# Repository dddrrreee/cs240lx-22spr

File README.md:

## CS240lx: advanced operating system lab, accelerated
### Engler + Akshay, Spr 2022.

tl;dr index:

  - [This is a lab class and here are the labs](./labs/README.md).
  - [Course website](https://github.com/dddrrreee/cs240lx-22spr).
  - [Course newsgroup](https://github.com/dddrrreee/cs240lx-22spr).
  - To get the repository: 

        git clone git@github.com:dddrrreee/cs240lx-22spr.git

    Put the path to the repo in your shell startup file:

    E.g. for `tcsh` I put the following in my `.tcshrc` file (and
    did `source ~/.tcshrc` after):
 
        setenv CS240LX_2022_PATH /home/engler/class/cs240lx-22spr/

    If these steps worked, you should be able to type `make` and have
    it work.

This is a implementation-heavy, lab-based class that will cover similar
topics as CS240 --- threads, virtual memory, file systems and distributed
systems --- but by writing code versus discussing papers.  After taking an
initial operating systems course you are often left in the odd situation
of having spent significant time getting the background knowledge needed
to do interesting actions, but not being left with enough time to actually
do them.  This course attacks this problem by assuming basic knowledge and
using it as a springboard to advance quickly through a set of powerful,
useful techniques that even advanced practioners can be ignorant of.

We will write custom code from scratch for the widely-used, ARM-based
raspberry pi; our code will run "bare-metal" without an operating system,
which means we can do interesting things without constantly fighting
with a lumbering OS that cannot get out of its own way.

By combining research insights (many unpublished) and our our lightweight
bare-metal code we will be in the unusual position of having foundational
abilities that most people have assumed are in-practice impossible.
As one example, we will implement fast, flexible exception handling
and then use this ability to build a variety of tools that find race
conditions, check code correctness, and memory  corruption.  By using
exceptions rather than binary rewriting we can build tools that find
similar errors as Purify / Valgrind, but can be implemented in merely
hundreds rather than hundreds of thousands of lines of code; our tools
will also be faster and more extensible.

Our initial plan was to do ten projects, one per week, where each project
covers two labs of (at a minimum) several hours each and a non-trivial
amount of outside work.

The course workload is significant, but I will aim to not waste your time.
CS140E is strongly encouraged as a prerequisite, but a sufficiently
talented and motivated implementor can make up for its lack.

I'm teaching this course because doing CS140E was was so much fun.
Each time I drove into lab, I would get an idea for one or two additional
labs I really wanted to do, and each time I wrote up an lab there would
be a long `NOTES.txt` of additional ideas.  After last year and this, I
have a big document of all the possible ideas.  This class will implement
the ones that seem the most interesting.

Also, we have Akshay for another quarter as a TA so it seems sensible
to exploit that happy fact!

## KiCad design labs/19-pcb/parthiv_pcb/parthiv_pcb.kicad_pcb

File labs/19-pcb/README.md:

# PCB (KiCAD) Lab by Parthiv

This lab is focused on designing printed circuit boards (PCBs), which you may find useful in your final project. This is moreso a quick lesson on how to replace your bundles of wires with a more reliable board, rather than how to actually design electrical circuits on a board which is a much more involved discussion. 

Our goal is to create a board that can plug into the Raspberry Pi GPIO header and connect to the USB/UART converter and 2 NRFs. You can also optionally add other devices to the board of your choosing. My board looks something like this:

You can see the GPIO header on the bottom and various headers on the top to connect other devices.

A sample PCB project that contains the board above can be found in `parthiv_pcb/`. You can refer to this if you ever run into a wall for how to proceed.

## Step 0: Installation

Please follow the instructions at [https://www.kicad.org/download/](https://www.kicad.org/download/) for your OS. It is open source so it should be possible but potentially annoying to build if your OS isn't listed.

### General Keyboard Shortcuts
I assume `Ctrl` becomes `Cmd` on mac.

* `Ctrl+S`: Save (do often!)
* `Ctrl+Z`: Undo
* `Ctrl+Y`: Redo
## Step 1: Creating a Project

1. Open up KiCAD (either type `kicad` in your terminal or search for it in your installed applications).
2. Go to File->New Project. Select a location where you want to create the project (you can do it in this directory) and give it a name. Ensure that the box to "Create a new folder for the project" is selected. Create the project.
3. You should see a window like this:

    On the left side, you can see a file called [project_name].kicad_pcb and another file called [project_name].kicad_sch. Double clicking these will open the PCB and Schematic editors respectively. 

## Step 2: Creating your Schematic

1. In the main KiCAD window, double click the .kicad_sch file to open the Schematic editor. You will see a blank schematic:

The schematic is where we will describe what pins of what components connect to what other pins of other components. You should try to keep it relatively organized if you can!

You can middle click and drag to move, or scroll up/down to zoom.

2. Go to Place->Add Symbol (or type the keyboard shortcut `A`). In the search bar, search for the symbol `Raspberry_Pi_2_3`. Select it, then click OK to start placing the component. Place it somewhere in the middle of the schematic by clicking. If you want to move it, you can click on it, hit `M`, and then move it around, then click again to place it. 

3. Now, we will connect the power rails of the Raspberry Pi. Hit `P` to open up the power symbol menu. Look for `GND` and hit OK to start placing the ground symbol. Put it near the bottom of the Raspberry Pi symbol. Hover over the end of one of the GND pins on the Pi, then hit `W` to start drawing a wire. Connect it to the GND symbol you just placed. Repeat this process for all the GND pins (see below).

Next, add power symbols for `+5V` and `+3V3` to the schematic, and connect those to the 5V and 3V3 pins of the Pi. Make sure you connect all pins of a given type together. We say 3V3 instead of 3.3V because in small text on a PCB, it may look like 33V. 3V3 is unambiguous.

4. Now that we've connected the power for the Pi, let's add some more components. Hit `A` again and find the `NRF24L01_Breakout` component, then place two of them. I would recommend putting them to the right of the Pi. Go ahead and connect the VCC to +3V3 and GND to GND.

5. Now, connect the NRF I/O pins to the Pi. For both NRFs, connect MOSI/MISO/SCK to the MOSI0/MISO0/SCK0 pins on the Pi. Also, connect the CSN of one to the Pi's CE0, and the CSN of the other to the Pi's CE1. Finally, connect the CE of each to two free GPIO pins (I chose 5 and 6). You can optionally also connect the IRQ pins to GPIO pins so you could have interrupt functionality, just make sure that each IRQ goes to a different GPIO.

6. The next step is to add a 10 uF coupling capacitor to each of the NRF power input pins to help smooth out the power supply to the NRF. Hit `A` and look for the `C_Polarized` part, and place one by each NRF. Connect the positive end of each to the NRF VCC, and the negative end to ground. Click on each capacitor and hit `E` to edit the properties. Set the value of each capacitor to `10 uF`. See the screenshot at the end of this section for what it should look like when you're done. 

7. Now, let's create a connector for our USB/UART chip so we can plug it directly into the PCB. We'll want to create a symbol to represent the logical pins that the USB/UART has. Go to Tools->Symbol Editor. You will see a blank symbol editor like this:

On the left, you can see various symbol libraries which contain different default parts that are common enough to be included in KiCAD. We will be creating a new one.

8. In the symbol editor, go to File->New Library. If you make it Project, any parts you make will only be usable in the current project. If you make it Global, you can use it in future projects. I went with Project but either is ok. Give it whatever name you want (`cs340lx_pcb`, or something)

9. On the left window, find the library you just created and right click on it. Then click New Symbol, and you'll see a window pop up. See below for recommended settings.

Click on OK and create it. 

10. On the very left (past the list of libraries), right click on the grid and select Grid Properties. 

In the window that shows up, change Current Grid to 2.54mm. This will prevent the weird alignment issues we had during lab.

11. On the right side, select the Draw a Rectangle tool and draw a rectangle on the screen. Don't worry, you can change it later. If you want to move the auto-generated text (`UART` and `J`), you can click on it (press escape to reach select mode like in the schematic editor) and hit `M` to move it. Click to place.

12. Now, we will add the pins. Hit `P` to create a pin. We'll make the `GND` pin, which is pin number 4 (4th from the top of the UART) and is a Power Output.

Place the pin down at the bottom of the rectangle, ensuring that the circle end of the pin is facing out (this is where you'll connect wires in the schematic).

13. Create the remaining 4 pins:

- 1: 3V3, power output
- 2: TX, output
- 3: RX, input
- 4: GND, power output (already did in step 11)
- 5: 5V, power output

Try to keep voltage at the top, ground at the bottom, and signals on the sides (like the Raspberry Pi symbol). You can grow and shrink the rectangle if needed by going to the select tool (escape). Your symbol should look something like this (doesn't have to match exactly). You can rotate a pin with `R` and move with `M` like you'd expect.

14. Once you've finished the UART symbol, save with Ctrl-S or Command-S, then exit the symbol editor. In the schematic editor, click `A` to add a symbol. Search for the UART you just created; you should see it pop up.

Connect the 5V pin to your +5V rail, GND to GND, TX to the Pi RX and RX to the Pi TX. You can optionally connect 3V3 to +3V3, but this isn't strictly necessary since the Pi also creates its own 3V3 on the pins.

15. Hover over an unused pin on the Pi and hit `Q` to mark it as a No-Connect (looks like an X). This declares that you meant to not connect this pin and didn't just forget to connect it. Now, you're in no-connect placing mode and you can click on all the unused pins on the Pi/UART/NRFs. Compare your schematic against the Completed Schematic section below, making sure that everything is connected the way it should be.

16. At this point, you are almost ready to edit the PCB. Here is the easiest point to go ahead and add more parts to your schematic; for example, if you want to add more sensors/devices. Make sure that when you create symbols, you assign pin numbers correctly so that it makes later steps easier.

17. Annotate the schematic with `Tools->Annotate Schematic`. A window will pop up, click Annotate, which assigns reference designators (`C1`, `J2`, etc) to all the symbols. 

18. Now, go to `Inspect->Electrical Rules Checker` and click Run ERC to run the ERC. Make sure you annotate the schematic first (step 17); otherwise, you get a ton of weird errors. This is like the compiler in software; it will catch violations of electrical rules (syntax) but NOT correctness. And sometimes it gets things wrong, which you will see.

You will hopefully see 2-3 errors. If you connected the UART 3V3 to +3V3, you will not get the first error I have. This error is because whoever made the Raspberry Pi Symbol decided to make the 3V3 pin a power input even though it's a power output. So the ERC thinks nobody is providing power to +3V3. We know this to be wrong (the Pi outputs 3V3) so we can ignore this.

The other error, saying that two outputs (both MISOs) are connected, can also be ignored. It is true that both NRFs output to their MISO pins, but semantically we know that only one will be doing so at a time (when its CSN is low).

If you have other errors, address them and re-run ERC. A common error is forgetting to put a no-connect on a pin in step 15.

19. The last step is to assign footprints, which are the representation of each symbol in the real world PCB. Go to `Tools->Assign Footprints`, which will open a new window. 

You will see that 2 of the 6 components (the NRFs) have footprints already assigned. We need to assign footprints for the other 4. Click on the row with C1, then on the left side look for library `Capacitor_SMD` (capacitor, surface mount device). On the right side, look for footprint `Capacitor_SMD:CP_Elec_4x5.4`. This corresponds to a capacitor with diameter 4mm and length 5.4mm, which is the size of [this 10uF capacitor](https://jlcpcb.com/partdetail/HonorElec-RVT1E100M0405/C3343) from the manufacturer we will use to assemble our boards (JLCPCB). Double click on `Capacitor_SMD:CP_Elec_4x5.4`, which will assign that footprint to our capacitor.

20. Go through and do this for all the components:

- Both capacitors: `Capacitor_SMD:CP_Elec_4x5.4`
- Pi: Library `Connector_PinSocket_2.54mm`, footprint `Connector_PinSocket_2.54mm:PinSocket_2x20_P2.54mm_Vertical` (0.1" female header, 2x20)
- UART: Library `Connector_PinSocket_2.54mm`, footprint `Connector_PinSocket_2.54mm:PinSocket_1x05_P2.54mm_Horizontal` (0.1" female 90 degree heder, 1x5).

Make sure it matches below. 

Then click "Apply, Save Schematic & Continue". You can then close out of the Assign Footprints window and the schematic editor.

### Completed Schematic

When you're done, your schematic should look something like this:

### Schematic Editor Keyboard Shortcuts

* `A`: add symbol
* `P`: add power symbol
* `Esc`: go to regular mouse (select) mode
* `M`: move (after selecting a symbol)
* `R`: rotate (after selecting a symbol)
* `E`: edit symbol properties (after selecting a symbol)
* `Q`: place no-connect symbol (should be in select mode first)
* `W`: draw wire (should be in select mode first)

### Schematic Editor Tools

* Tools->Symbol Editor: create new symbols
* Tools->Annotate Schematic: assign reference designators
* Tools->Assign Footprints: assign PCB footprints to schematic symbols
* Inspect->Electrical Rules Checker: validate against some rules

### Footprint Editor Keyboard Shortcuts

* `P`: add pin
* `Esc`: go to regular mouse (select) mode
* `M`: move (after selecting a symbol)
* `R`: rotate (after selecting a symbol)

## Step 2: Create PCB

Now, the fun begins -- time to create the PCB. For all of these steps, you don't have to match the exact thing I do. Actually better if you don't, so it's your board and not you making my board :D

1. From the KiCAD main window, double click the .kicad_pcb file to open the PCB editor. You will see a blank PCB, this time a black background instead of white (schematic).

You can middle click and drag to move, or scroll up/down to zoom.

2. Go to Tools->Update PCB From Schematic. This will open a window, click "Update PCB". Hopefully, there are zero warnings/errors. 

A common error is forgetting to assign a footprint to a symbol in the schematic. If you do this, then KiCAD is unsure what physical footprint to assign to the logical symbol you created in the schematic. Revisit step 19 from part 1 if this happens. Then, come back to the PCB viewer and this step again.

If you have zero warnings/errors, then you can "Close" the window that popped up, and then click anywhere to place the mess of components.

You will see a 2x20 pin header for the Pi, 1x5 header for the UART, two 2x4 headers for the NRFs, and two capacitors.

3. If you look at the picture at the very top of this page, you will see that the Pi header is on the underside of the board whereas everything else is on the top. To move the Pi connector to the backside of the board, click on it, then hit `F` to "flip" it to the back. You will see the outline change from pink to blue, and also the text related to the Pi header will be mirrored. 

You can also go to View->3D viewer to see this, though there will probably be an error about not having a board outline yet (which we will fix soon).

4. Now, we will try to organize the components reasonably well to minimize the length of the connections we need to make. Hit `Esc` to go to select mode, then click on any footprint. Once you've selected the footprint, you can rotate it with `R` or move it with `M`. Click to place when you're in move mode. 

All of the thin white lines you see connecting the different pins of components are connections we will eventually need to make, so trying to keep these as "untangled" as possible will make things easier. That being said, it's probably impossible to completely avoid crossing (it's not an issue to have crossing wires as we have two layers).

I would recommend putting the Pi header at the top of the other components, with the +5V pads to the left. Then, put the UART near the left side of the Pi header (so there's a short path for +5V).

Also, make sure to keep each capacitor close to the +3V3 pad of one of the NRFs. Technically, the way that our schematic is, we could connect them to anywhere on +3V3 and GND. However, we would like to keep the resistance on the path between the capacitor and the NRF as small as possible, so that the capacitor can deliver power to the NRF when it has current spikes during transmit. Here's one possible arrangement which is pretty reasonable:

In lab I also told people you can put the capacitors "underneath" the NRFs. Since the NRF is quite high off the board with its header, and the capacitors are short, you can go for that if you'd like as it'd help save board space.

5. Let's draw the outline for our board. On the right side, you will see a bunch of Layers

These each represent a different layer of the PCB. Some highlights:
* `F` and `B` prefixes are for front and back, as we can have many things on either side of the board
* `Cu`: front and back copper, which are where we make our connections
* `Adhesive`: some components are glued to the board, this layer shows where the glue should be placed
* `Paste`: for surface-mount components, this is where the machine will automatically place solder paste. After components are automatically placed in their locations, the whole board is baked, melting the solder paste, then cooled, hardening the paste (and making electrical/mechanical connection with the components).
* `Silkscreen`: text/drawings that are printed on the board for aesthetic/documentation reasons
* `Mask`: The green (or other color) layer of the board which protects the underlying copper from corrosion and accidental shorts. It's expected that most of the board has mask, so the `Mask` layer is actually the negative. So it shows where there is _not_ mask.
* `User.*`: these don't get printed, so you can put stuff for documentation
* `Edge.Cuts`: the edges of the board which are cut.
* `Courtyard`: bounding polygons for the various components. Ideally, no courtyards overlap so we can ensure that no components are inside each other. Just like we had an ERC in schematic, we have a DRC (design rules check) for the PCB which will complain if two courtyards overlap. However sometimes we know that we are safe (e.g. capacitor fits "under" NRF).

You can enable/disable the visibility of layers by clicking the eye icon, which can be interesting. 

You'll want to click on the `Edge.Cuts` layer and make sure the triangle is pointing to it (like in the image above). Select the rectangle tool (also selected in the image above). Now, draw a rectangle around the components you made by clicking once for one corner, then clicking again for the opposite corner. Give your self some extra space for routing traces (wires) around the components. 

Now, if you open Tools->3D Viewer, you will see your new outline.

If you make it too big/too small, you can always edit this by clicking on the `Edge.Cuts` layer, then the select tool (`Esc`), then clicking on the corner of the rectangle and changing the shape. 

You can also make a custom shape using a vector graphics tool like inkscape, then export as SVG. Then go to File->Import->Graphics and add your shape to the `Edge.Cuts` layer.

6. A common practice in PCB design is to make (almost) the entire front of the board be connected to your power rail, and (almost) the entire back of the board be connected to your ground rail (or vice versa). This helps you avoid having to manually connect every power and ground together, sort of like how we just connected them to the GND and +3V3 symbols on the schematic to avoid a ratsnest of wires between the power pins.

We will do that now. Click on the `F.Cu` layer and do `Ctrl+Shift+Z` (mac may be `Cmd` instead of `Ctrl`) to open a window for "copper zone". Ensure that the `F.Cu` layer is selected on the left, then select the `+3V3` net.

Hit OK, then draw a rectangle that's bigger than the rectangle you drew for the edge cuts (this time, you need to click all 4 corners, not just 2 opposite). Repeat the process for `B.Cu` and `GND`. It should look something like this when you're done:

If you mess up while you're drawing, you can hit `Esc` and try again.

7. Let's actually fill the zones to make the electrical connections. Hit `B` to fill zones. This should hopefully connect almost all of our +3V3 and GND connections for us! You'll see the white connection lines for those disappear. If you zoom in to some pins, you will see what exactly happened:

Notice that on the front side (red), where we made the 3V3 zone, KiCAD helpfully connected the pin with an X pattern. On the back side (blue), where we made the GND zone, KiCAD connected with a + pattern. it may be easier to see what's going on if you make one of the two copper layers invisible (see step 5). Make sure to turn it back on afterwards.

8. Let's setup the schematic editor to be ready to route the traces (wires) we use to make electrical connections. Go to the top-left corner, where it says `Track: use netclass width`. Click this and do `Edit predefined sizes`. Add widths of `0.25 mm` and `1 mm`. 

Hit OK. On the top left under `Track: use netclass width`, you can now select those two sizes. We will use `1 mm` tracks for power and `0.25 mm` for signals. Wider tracks have lower resistance (good for high current) but are harder to route. 

9. Now the fun begins: time to route our traces! Click on `F.Cu` on the left to route on the front of the board. Then, select a `1 mm` trace width. Move your mouse over the +5V pad on the UART (you can zoom with scroll wheel, and middle click+drag to pan). Hit `X` to enter trace mode. If you move your mouse, you will see a trace expanding out of the pad.

Each time you click in trace mode, you will "save" some of your progress that you've made. Once you reach your target, you can click on it to finish routing the trace. In general, try to avoid 90 degree turns. 

Go ahead and connect the 5V from the UART to both Pi 5V pins. Then, hit `B` to re-fill the zones, and you'll see a bit of the 3V3 zone has been cleared out to allow the trace you just made to go through it. Make sure you give a bit of clearance from the 3V3 pad of the Pi so that you don't cut it off from the 3V3 plane.

Make sure your trace is similarly THICC as mine, as otherwise it will get very warm due to lots of current! The whole Pi's power comes through this trace. 

10. Let's now route the other 2 UART connections. You can click the `B.Cu` or just hit `V` to swap to the back layer (the board should look blue instead of red).

I routed the first signal as below. I would recommend changing the Grid at the top of the screen to 0.05 inches instead of the default 0.1 inches.

I started routing the second signal, but oh no! The wires have to cross. I hid the F.Cu layer for ease of visibility of what's going on.

Well, we have two layers! We could, for example, bring the signal to the front of the board and have it cross the other one there. We first need to create a "via", which is a hole used to route the signal between the two layers. Hit `Ctrl+Shift+V` (mac may be `Cmd` instead of `Ctrl`) to go to via mode, then click on the end of the track to place the via there. 

Make sure that you are not putting the via into another trace on the other side of the board. If you need to move your trace, you can enter select mode with `Esc`, make sure that you are on the correct layer (either click on right side or hit `V` to swap layers), then click the trace, then hit `Del` to delete it. Then, you can hit `X` again after mousing over the start of wherever you'd like to re-route from. Make sure you select the right trace size first :)

Now, you can flip over to the other side of the board (click on the right, or `V`) and then hit `X` while hovering over the via to continue routing from the via. 

You can examine the result in 3D viewer as well. I'd recommend religiously clicking B after you route traces/create vias to make sure that what the zones are doing makes sense.

As was discussed in lab, it's also possible to smartly route the traces in between the Pi's pins, thereby avoiding the whole via thing. But this is helpful to show now as the routing becomes much more complicated for the SPI signals on the NRF.

11. We want to go and connect the capacitor ground pads to the backside ground plane. Since the capacitors are surface mount components, they have pads on only the frontside. Compare this with the through hole pins on everything else, which can be connected to both the front and back. 

What can we use to connect back/front? Yep, vias! You can see I also moved my capacitors from before to try and make the path from cap->NRF as short as possible. 

But you may see that the vias were automatically assigned to the 3V3 net instead of GND (maybe not for you, but it was for me). If this happens, you can just go to select mode (`Esc`), then select the via, then hit `E` to edit properties, then change the net to `GND` instead of `+3V3`. Do this for each via, and you should see that the capacitor missing connection from the GND pin now connects to the via instead of the NRF ground pin. I'd also recommend making an actual trace from the capacitor to the 3V3, so that the connection is a bit wider than the little connection that is auto-created.

12. OK! Now it's time for you to go and route the rest of the traces as needed. Go ahead and switch the trace width to 0.25mm. Make sure you address every one of the white lines (they should all disappear by the time you're done). This is more of an art than a science, and you will get better as you practice. See the Routing Tips section below for some ideas.

Here is my finished routing (you can also see the `parthiv_pcb/` folder for my project). 

13. Now, let's add some text to our silkscreen so we can remember what is going on on our board. First, open Tools->3D Viewer to see what is already on there.

This is ok, since we can at least correlate vs. our schematic with the same reference designators. But perhaps you'd like to add more. If you select `F.Silkscreen` on the right side, you can then go to the Text tool (`Ctrl+Shift+T`) and add text. Click to open a menu where you can type text.

Some helpful things to consider: UART pins so you know what orientation to put it. Maybe also NRF pins so you can remember what's connected to what. Also put your name on it somewhere!

14. Almost done with the board! Let's run DRC (design rules checker) which will make sure our board is manufacturable. Go to Inspect->Design Rules Checker. In the window that pops up, enable "Test for parity between PCB and schematic" just to be sure.

Click Run DRC. If you have errors, go to the DRC Errors section below for common errors. For each, I'd recommend you zoom in super close, then click the entry in the DRC window. You will see an arrow in the middle of your screen. Address the issue and then click Run DRC in the window again. If there are other errors send a screenshot to me (parthiv at stanford) and I can help you out. Eventually, you will get a clean DRC.

### Routing Tips

#### Clearance
Try to give clearance to pads and don't route traces too close to them (especially ones that connect to planes). This makes it easier in the future to route signals from those pads.

#### Try, try, try again

Don't be afraid to delete an old trace and re-route it if you find you need to move it to make something else work.

#### Zone Islands
An extremely common issue that people ran into was creating a filled zone "island", like below: 

Notice how the two traces have created an almost closed-loop, which cuts off a section of the filled zone into an island that's disconnected from the rest. An easy fix is to open the closed loop by moving one or more of the segments of the traces onto the other layer. If you go to the select mode (`Esc`), then click on a piece of trace, then hit `E`, then swap the layer to the other layer. You can then go and place vias (`Ctrl+Shift+V`, or `Cmd+Shift+V` for mac?) on each end of the segment that you flipped to the other side to make electrical connection.

Another (worse) solution is to to put a via on the island and off the island and route a "jump" on the other side of the board. This isn't really recommended though, since it means there is higher resistance on the power plane (vias introduce resistance).

### DRC Errors

Here are some common DRC errors/warnings

#### Track has unconnected end

You have some track that is only connected on one side and can just be deleted. A tricky one is when the track is contained entirely inside a pad hole, so it's invisible (see below). Just click on the exact tip of the arrow that is pointing out the error and it should get highlighted. Then just hit `Del`. It helps to be VERY zoomed in on the PCB editor window.

#### Silkscreen clipped by solder mask

You have silkscreen that is either drawn off the edge of the board, or overlaps a pad somehow. Either expand your board (go to `Edge.Cuts` layer, then `Esc` to select, then click and expand the rectangle). Or move the silkscreen item (go to appropriate `*.Silkscreen` layer, then `Esc` to select, then click item, then `M` to move it). Below you can see I drew my board too small so the silkscreen hangs off the edge.

### PCB Editor Keyboard Shortcuts
* `Esc`: go to regular mouse (select) mode
* `M`: move (after selecting a footprint)
* `R`: rotate (after selecting a footprint)
* `F`: flip footprint (after selecting a footprint)
* `Ctrl+Shift+Z` (or `Cmd+Shift+Z` on Mac?): create filled zone
* `B`: fill zones
* `X`: route trace
* `V`: swap active copper layer (front to back or vice versa)
* `Ctrl+Shift+V` (or `Cmd+Shift+V` on Mac?): create via
* `E`: edit properties
* `Ctrl+Shift+T` (or `Cmd+Shift+T` on Mac?): add text (in silkscreen layer)

### PCB Editor Tools
* Tools->Update PCB From Schematic: Apply any updates from the schematic editor (make sure to save in schematic editor)
* View-3D Viewer: view a 3D model of your board
* Inspect->Design Rules Checker: validate that it's manufacturable

## Step 3: Manufacture with JLCPCB

We are ready now to manufacture the board! [JLCPCB](https://jlcpcb.com) is an inexpensive PCB house that also has parts/assembly, so we'll be using them. 

1. Install [this KiCAD plugin](https://github.com/Bouni/kicad-jlcpcb-tools) that helps us generate the files that JLCPCB needs. Follow the instructions there for installation (either method is ok, git clone is probably easier). Then restart KiCAD.

2. In the PCB Editor, go to to Tools->External Plugins->JLCPCB Tools. You will see a window with the 6 parts on our board.

3. We are only having JLCPCB assemble the surface mount parts (just the capacitors in this case). So go ahead and highlight the other 4 non-capacitor parts (shift-click to select multiple), and click the `Toggle BOM/POS` button so that they have Xs next to them. This will exclude those parts from the files we upload to tell JLCPCB how to assemble the board, since we will assemble the pin headers by hand.

3. Click the `Update library` button to download the JLCPCB parts library. This takes a bit ~30-60 secs depending on your internet.

4. Highlight the 2 capacitors (shift-click to select multiple). Then click the `Select part` button. Recall from earlier we chose [this 10uF capacitor](https://jlcpcb.com/partdetail/HonorElec-RVT1E100M0405/C3343). Therefore, in the window that pops up, search for keyword `C3343` (the JLCPCB part number for that component). Highlight the top result (verify it's correct) then hit `Select part`.

5. Verify that your BOM (bill of materials) looks like this

Then, click `Generate fabrication files` in the top right. In your project directory, you should now see a `jlcpcb` subdirectory containing `assembly` and `gerber` subdirectories. 

6. Navigate to [jlcpcb.com](https://jlcpcb.com), then click "Order now" in the top right. 

7. Click on "Add gerber file", then upload `<project_directory>/jlcpcb/gerber/GERBER-<project_name>.zip` (make sure it's the zip, not an individual gerber file). You should see your board in the website!

Note, the capacitors won't be there yet (this is just the board).

8. Go through the options. Most things can stay as the default, but perhaps you want to change the PCB color! Non green is the same price but takes a bit longer. Most likely, it is only $2 for the boards unless you made something super big or start messing with the options.

9. Keep scrolling, and "turn on" the slider next to PCB Assembly.

You can leave all the options as default, just make sure you are assembling on the top side. You could optionally enable "Confirm Parts Placement" if you want someone to give your board a lookover before assembling. Click the big "NEXT" button on the right side. It will prompt you to make an account (can just sign in with google).

10. In the next page, you will need to upload two files. 

- The first is the BOM (bill of materials) which contains the correspondence between reference designators (`C1` and `C2`) and the actual part JLCPCB number (`C3343`). This is located at `<project_directory>/jlcpcb/assembly/BOM-<project_name>.csv`.
- The second is the CPL (component placement list) which contains the X/Y coordinates of each reference designator. This is located at `<project_directory>/jlcpcb/assembly/POS-<project_name>.csv`. Note that the file is called POS for position, not CPL. Oh well.

11. In the dropdown menu, select an appropriate usage description. I just do `Reserch\Education\DIY\Entertainment -> DIY HS Code 902300` (spelling errors are theirs not mine). Then hit `NEXT`. 

12. On the next page, validate that the correct part was detected. You can click the "Matched Part Detail" and verify.

Hit "NEXT".

13. You will get a 3D view, similar to the KiCAD 3D viewer. However, this time it just shows the board and the 2 capacitors that JLCPCB will assemble. Ensure that they are in the correct spot. 

14. Click "Save To Cart". You're done and can order! It would take ~1 week to arrive.

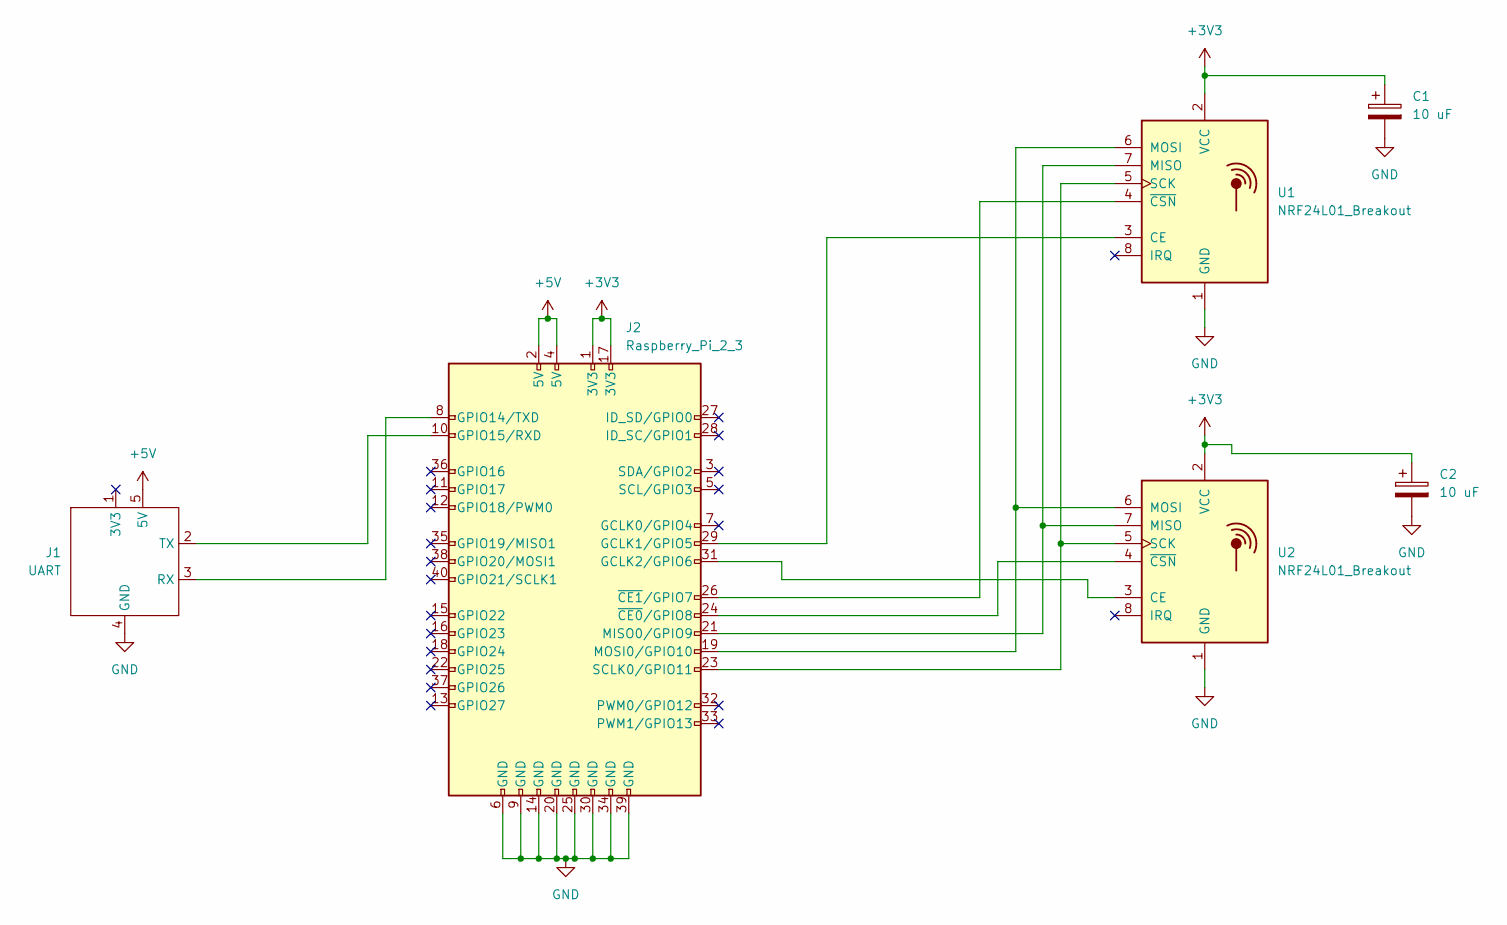
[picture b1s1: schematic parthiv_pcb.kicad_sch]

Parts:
C1, C2: 10 uF; CP_Elec_4x5.4
J1: UART; PinSocket_1x05_P2.54mm_Horizontal
J2: Raspberry_Pi_2_3; PinSocket_2x20_P2.54mm_Vertical
U1, U2: NRF24L01_Breakout; nRF24L01_Breakout

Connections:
+3V3: C1.1, C2.1, J2.1 (3V3), J2.17 (3V3), U1.2 (VCC), U2.2 (VCC)
+5V: J1.5 (5V), J2.2 (5V), J2.4 (5V)
GND: C1.2, C2.2, J1.4 (GND), J2.6 (GND), J2.9 (GND), J2.14 (GND), J2.20 (GND), J2.25 (GND), J2.30 (GND), J2.34 (GND), J2.39 (GND), U1.1 (GND), U2.1 (GND)
unnamed: J1.2 (TX), J2.10 (GPIO15/RXD)
unnamed: J1.3 (RX), J2.8 (GPIO14/TXD)
unnamed: J2.19 (MOSI0/GPIO10), U1.6 (MOSI), U2.6 (MOSI)
unnamed: J2.21 (MISO0/GPIO9), U1.7 (MISO), U2.7 (MISO)
unnamed: J2.23 (SCLK0/GPIO11), U1.5 (SCK), U2.5 (SCK)
unnamed: J2.24 (~CE0/GPIO8), U2.4 (~CSN)
unnamed: J2.26 (~CE1/GPIO7), U1.4 (~CSN)
unnamed: J2.29 (GCLK1/GPIO5), U1.3 (CE)
unnamed: J2.31 (GCLK2/GPIO6), U2.3 (CE)

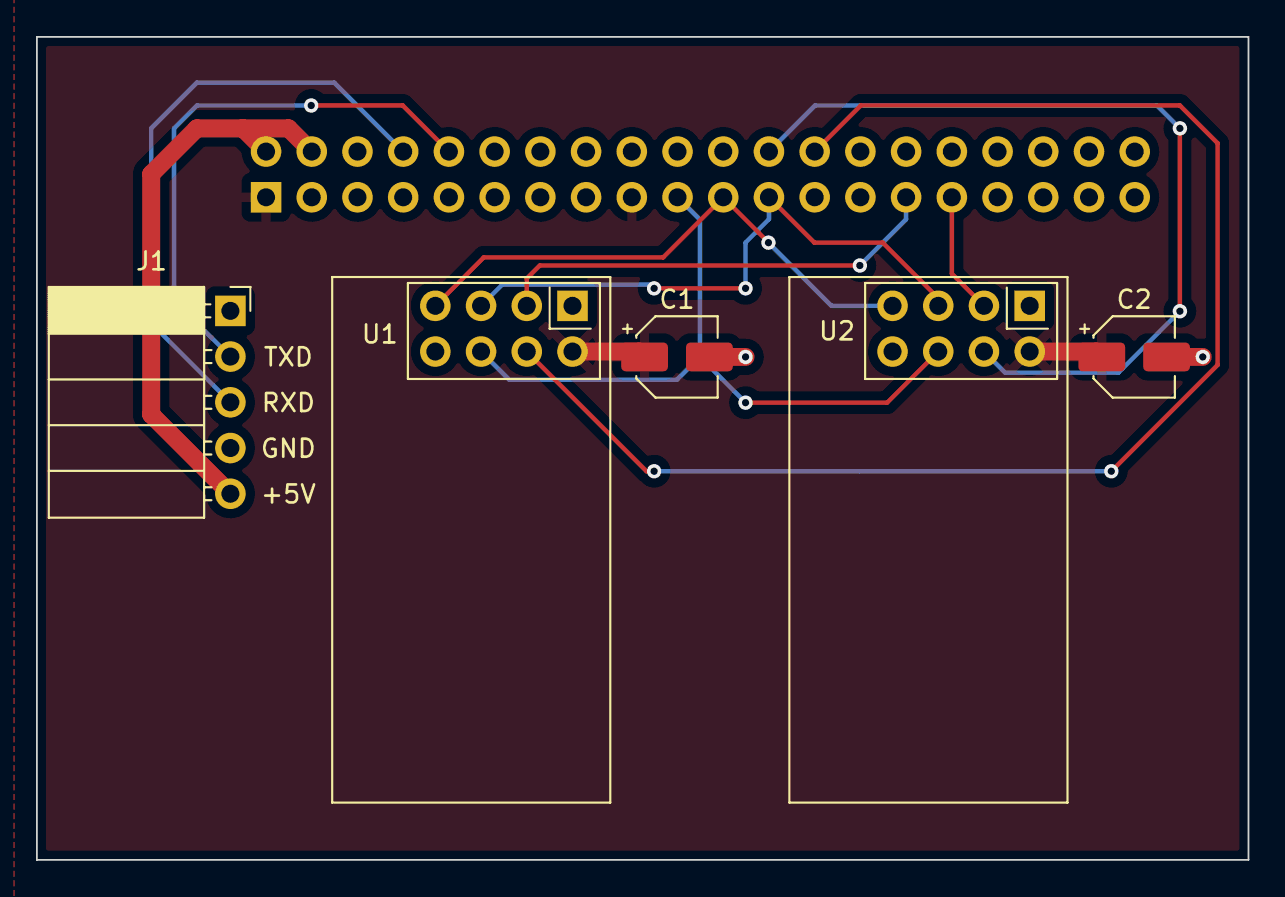
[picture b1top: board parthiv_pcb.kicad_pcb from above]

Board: 2 copper layers, 67.3 x 45.7 mm, 6 parts (1 on the bottom side), 12 nets.

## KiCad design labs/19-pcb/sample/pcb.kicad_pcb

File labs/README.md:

## Labs.

This is a partial set of possible labs.  They've been split into ones
we'll almost certainly do and those that we might do depending on
interest.  I'm going through old notes and TODO files pulling in more,
so check back :)

There are way more possible labs than class slots so if you can please
look through these before the first class and see which you prefer.

In either case, these are a ***tentative*** set of labs.  They will
change!  Some will get dropped.  Some will get added.  All will get
modified significantly.

This is the second offering of the class.  While we have done many of
the labs once before in cs240lx or cs340lx many ideas are research-paper
level and how to best implement them is still up in the air, so the only
constant will be change.

----------------------------------------------------------------------------
##### low level code module

  - [1-dynamic-code-gen](1-dynamic-code-gen/README.md): you'll learn
    how to generate executable machine code at runtime and how to 
    use this trick to do neat stuff.  

    Possible things to build:
      - generate exact cycle write schedules where you give a set
        of reads and writes and the cycle they should occur at.
      - do real generic routines in C where you "curry" a parameter
        into a runtime thunk that calls the original routine.  this
        for example lets you replace `int foo(a,b,c)` with `int fp()` and, thus
        have a set of data structure routines that can work on routines
        that take no parameters and return an `int` rather than needing to 
        make (for example) an iterator routine for each different 
        data-structure.
      - simple packet filter JIT engine --- these are being heavily used
        in linux for monitoring.  could do BPF (what they use) or our own.
      - 

  - speed stuff [below]: open question: can be enable caching when no
    VM?  Not sure where to place this.

MAYBE:
  - linker script hacks.
  - bootloader that can copy itself out of the way + use this to 
    make a network bootloader.
  - a runtime code gen system that can work on riscv, x86, arm,
    etc.

---------------------------------------------------------------------
### Simple binary-analysis tools.

As we showed in cs140E, you can use debugging hardware to make powerful
binary analysis tools that normally take on the order of 1MLOC of code.

We will build the following:

  - [Trap-based Eraser]: Eraser is a famous race detection tool that
    uses binary-rewriting to instrumenting every load and store and
    flagging if a thread accessed the memory with inconsistent set of
    locks (its *lockset*).  Doing binary rewriting is hard.  By using
    debugging hardware and fast traps we can build a version in a few
    hundred lines of code: simply trap on every load and store and
    implement the lockset algorithm.
  
  - [Trap-based memory checking]: Valgrind dynamically rewrites binaries
    so that it can instruments every load and store.  Dynamically
    rewriting binary is harder in some ways than the static rewriting
    that Eraser does, which was already really hard.  You will use your
    traps to implement a much simpler method:

    - Mark all heap memory as unavailable.
    - In the trap handler, determine if the faulting address is in bounds.
    - If so: do the load or store and return.
    - If not: give an error.

    Given how fast our traps are, and how slow valgrind is, your approach
    may actually be faster.
   
    To get around the need for *referents* (that track which block of
    memory a pointer is supposed to point to) you'll use randomized
    allocation and multiple runs.

  - [Thorough conconcurrency checking]: we will use traps to build a simple,
    very thorough lock-free checking tool.  Given a lock free algorithm and
    two threads:

    - Mark its memory as inaccessible.
    - On each resulting fault, do the instruction but then context switch
      to another thread.
    - At the end, record the result.
    - Then rerun the thread code from a clean initial state without doing
      context switches.   For the type of code we run: Any difference
      is an error.

    To be really fancy, we can buffer up the stores that are done and
    then try all possible legal orders of them when the other thread
    does a load.  This checker should find a lot of bugs.

    To speed up checking we use state hashing to prune out redundant
    states: at each program counter value, hash all previous stores,
    if we get the same hash as before, we know we will compute the same
    results as a previous and can stop exploring.

  - [Possible: Volatile cross-checking] A common, nasty problem in
    embedded code is that programs code use raw pointers to manipulate
    device memory, but either the programmer does not use `volatile`
    correctly or the compiler has a bug.  We can detect such things with
    a simple hack:

    - We know that device references should remain the same no matter
      how the code is compiled.
    - So compile a piece of code multiple ways: with no optimization, `-O`,
    `-O2`, with fancier flags, etc.
    - Then run each different version, using ARM domain tricks to trace
      all address / values that are read and written.
    - Compare these: any difference signals a bug.

    This tool would have caught many errors we made when designing cs107e;
    some of them took days to track down.

   - There is a ton of other possible tools.  Might do more.

---------------------------------------------------------------------
##### Speed

Speed: in this class usually we waste a ton of cycles to buy simpicity
as a way to buy correctness.  ("The unavoidable price of correctness is
simplicity." --- Hoare.)

However, in this segment (probably 2 labs at least) we will change pace
and try to make your code as fast as possible.

Being able to speed things up is great; not always needed, but a fancy
tool if you can do it.

More importantly, speeding up our code --- which goes down to bare metal
(at the level of ASIDs, TLBs, different caches) and all the way up to
the OS and then application --- is a great way to deeply understand how
hardware and OS code actually work.

Time cuts across all boundaries so you cannot simply ignore ("abstract
away") pieces --- you have to understand each, and understand how
they interact.   Further, the process is ruthless with stupid: you
cannot fake it.  Either what you do cuts down time or it does not.
Optimization is a fun, limited example of "classical" science, where you
have to come up with hypotheses, act on these, and then do a completely
cut-and-dry experiment (run the code) that immediately cuts down the
bullshit or gives you some dopamine.

At a more conceptual level, making code as fast as possible requires
understanding its essence and cutting away the inessential.  The more
you understand, the faster you can go.  People that do not understand
much cannot write fast code --- everything is too much in shadow to find
the quick path.

With that said: "premature optimization is the root of all evil"
so we won't do this much.

  - Fast exceptions: Since our binary tools depend so much on exception
    handling we'll make it much more efficient.  Rip the code down to the
    bare minimum, enable icache, dcache, BTB, any other tuning you can.
    See how much faster you can make it compared to where we started.

  - Fast `libpi` code: you'll redo your statistical profiler from 140e and
    make it use backtraces to figure out where the code was called from.
    Using this you can speed up different pieces of `libpi` easily.

  - POSSIBLE: getting the maximum speed out of NRF24L01+.  You'll
    ping-pong packets between two devices and tune the code so that you
    get the maximum throughput possible. You can use the same tricks as
    for interrupts, but also play games with sending multiple packets
    in flight, using interrupts to help pipelining, etc.

  - POSSIBLE: Fast OS primitives.  If we build a simple OS it makes sense
    to tune its primitives.  We will run common micro-benchmarks on your
    laptop and see how much you can beat them by on the much-slower pi
    hardware using the much-faster code you wrote.    Example benchmarks:
    `fork()`, ping-pong across `pipe` implementations, cost of a
    protection fault, etc.  If you beat linux/macos by 50x I wouldn't
    be surprised.

---------------------------------------------------------------------
##### Timing-accurate code 

We couldn't afford to give everyone two r/pi's in 140e, but might be
able to squeek by in 240lx.  Which is great, b/c we can then build a
digital analyzer which is really useful.

  - [3-digital-analyzer](3-digital-analyzer/README.md): the pi is fast enough,
    and flexible enough that we can easily build a logic analyzer that
    (as far as I can tell) is faster --- and certainly more flexible ---
    then commercial logic analyzers that cost hundreds of dollars.
    You'll learn how to write consistently nanosecond accurate code.

    The digital analyzer can be viewed as a way to do `printf`
    for devices.  We'll use it to reverse engineer the SPI, I2C and
    UART protocols.  We'll also make it so you can upload code into
    it to do more interesting checks (e.g., that real time threads hit
    their schedules).

    A big challenge is getting the error / variance from one sample to
    another --- you'll use both memory protection tricks and interrupts
    to shrink the monitoring loop down far enough that it runs with an
    order of a few nanosecond error.

  - [ws2812b](ws2812b/README.md) you'll write nanosecond accurate
    code to control a WS2812B light string.  The WS2812B is fairly common,
    fairly cheap.  Each pixel has 8-bits of color (red-green-blue)
    and you can turn on individual lights in the array.

---------------------------------------------------------------------
##### Device code

You'll write some device drivers from scratch to get a better feel
for hardware.  Device driver code makes up 90+% of OS code, so it makes
sense to learn how to write this kind of code.   We'l likely do some
amount of building a fake-pi implementation to check this code.

  - [i2c-driver](i2c-driver/README.md): You'll use the broadcom
    document to write your own I2C implementation from scratch (no helper
    code) and delete ours.

    To help testing, you'll also write a driver for the popular ADS1115
    analog-to-digital converter (also from scratch).  Analog devices
    (that output a varying voltage) are typically the cheapest ones.
    Unfornately your r/pi cannot take their input directly.  We will
    use your I2C driver to read inputs from a microphone and control
    the light array with it.

  - [spi-driver]: SPI is a common, simple protocol.  You'll implement
    it and use it to control a digital-to-analogue converter and to
    control an OLED screen.

------------------------------------------------------------------
### Ideally: many other chips

We've written code on the r/pi A+, which is fine.  One thing I would love
to get out of this class is having the first set of 140E labs ported to
10+ other chips.  The tentative plan is to have a mid-term project where
you and some friends get a chip, get it up and running w/ a verson of our
bootloader and then writeup how to do so.  We'd then spend a monster week
of hacking having everyong write their code for every different chip.
The resulting portfolio should be extremely useful.

------------------------------------------------------------------
### POSSIBLE: RiscV

In cs340lx we spun up some hifive2 riscv boards and then wrote a simple
simulator that could run itself.  I later used this to make a symbolic
execution engine with a few hundred lines of code.  Using riscv is a
great method for doing binary analysis since its  a much simpler system
than ARM or valgrind intermediate representation.  We'll do several labs
building this.

------------------------------------------------------------------
### POSSIBLE: Protection domains

   - [Fast protection domains]: As you probably noticed, we have no
   protection against memory corruption.  As your system gets bigger,
   it becomes much much harder to track down which subsystem is causing
   everything to crash.  Going all the way to UNIX style processes
   is one attack on this problem, but we can use ARM do to a lighter
   weight method:

     1. Give each domain a unique domain number.
     2. Tag all memory associated with the domain with its domain number.
        (you may have to have additional domain numbers for pages accessible
        by more than one).
     3. Before you call into the domain, change the domain register so that
        domain has client privileges, but no other domain is accessible.
     4. At this point it can only touch its own memory.

   This method is much faster than switching between processes: we don't
   have to flush the TLB, caches, or page table.

   We'll do some tricks using linker scripts to make this relatively
   easy to setup.

   Subsystems corrupting and crashing systems is a serious problem in
   real OSes: 90% of their code is device drivers, and device driver
   code sucks.  A research system Nooks tried handle this problem by
   tracking the resources a device driver used, using compiler support
   to detect if the driver was about to corrupt memory --- at this point
   it would kill the driver and release its resources.  Given your OS
   we can build a version of this in a few hours.

------------------------------------------------------------------
### POSSIBLE: A tiny but complete OS

A big problem with cs140e is that we have a bunch of atomized pieces,
but didn't put everything into one working system.  We'll spend a few
labs getting a unix-ish simple system working that has virtual memory,
processes, inter-process communication, a simple file system etc.

   1. Build more of a small, somewhat "Turing complete" OS that can
      do interesting stuff: `sbrk` (and hence `malloc`), `pipe`,
      `waitpid`, a faster, more powerful version of `signal`, pre-emptive
      scheduling, some kind of real-time guarantees.

      One of the main points of this 140e/240lx/340lx is intentionally
      out of step with modern times: if you have a small code base you
      understand completely (e.g., b/c you wrote it) it's very very
      easy to do many things in a few hours that would warrant a full
      research paper and maybe more than a year of effort to build in
      a Linux or MacOS.  In many cases, you can build features that
      simply do not exist in current systems.    As one example of the
      former, in cs140e we built a `gprof` in about 60 lines of code.
      As examples of the latter: all of our memory tracing tools.

      As part of this genre I'm thinking in the next few labs we'll
      read two papers (one on memory tricks by Appel et al and one on
      "scheduler activations" by Bershad et al) and have you build
      those pieces.

      This approach will start to give you a more conceptual feel of key
      issues --- the papers are old, but the topics and tradeoffs are
      just as sharp today.  It will also show you currently actually
      have the tools to do research papers on your own --- proof by
      example since you will implement them!

      It also makes the value of a small code base clear: you should
      be able to bang these out in one medium lab each, despite modern
      OSes not being able to provide the functionality / efficiency
      they provide.  (Note: we will do the fast part soon.)

      Maybe your OS can't run many programs, but you can perform many
      actions that many (or all) cannot.

------------------------------------------------------------------
### POSSIBLE: A grab bag of things

  - have you write a simple static bug
    finding system based on "micro-grammars", a trick we came up with
    that does incomplete parsing of languages (so the parser is small
    --- a few hundred lines versus a million) but does it well enough
    that you can find many clean bugs with few false positives. It'd be
    fantastic if you guys could write your own system and go out and find
    a bunch of real bugs in the large systems you'll be dealing with.
    The main limit is me finding a few days to build this out and try
    to break it down in a way that doesn't require compiler background
    (this is feasible, I am just badly managing time).

  - Make supe tiny processes.  We can't run many programs, but we can
    make our processes orders of magnitude smaller than in other OSes.
    E.g., if we pin TLB entries we don't even need a page table!  If you
    then cut down on the size of the env structure and use small pages
    (either 4k or 1k) rather than 1MB you can make absolutely tiny
    processes.  I think we could run tens of thousands on the chip, which
    would be unheard of for any other OS on an equivalant sized system.
    This would be cool and teach a bunch (it's similar to the optimization
    we would do but would be for space vs time.)

  - Make a simple distributed system.  One use case is doing crypto
    mining on a linked set of r/pi chips.

  - As a way to help testing (among other things): do a real writeable
    file system so that we can save the binaries to run, the output,
    etc and use scripting (via FUSE) to easily interact with your pi
    through your normal shell.  We could also use the RF chip to make
    this distributed.

  - More speculatively: do very sleazy symbolic execution  to generate
    inputs to run code on (and, e.g., find differences in today's code
    versus yesterday's) by inferring what each machine instruction does by
    running it in its own address space, seeing how the registers change,
    how memory is read and written, and then matching this against known
    micro-ops (or compositions of them).  You can then use this to run
    the binary to get constraints and then use a constraint solver to
    solve them and rerun the result on the code.  If we can do this it
    will be a very powerful trick, since its simple enough to work in
    real life (unlike the current symbolic systems).

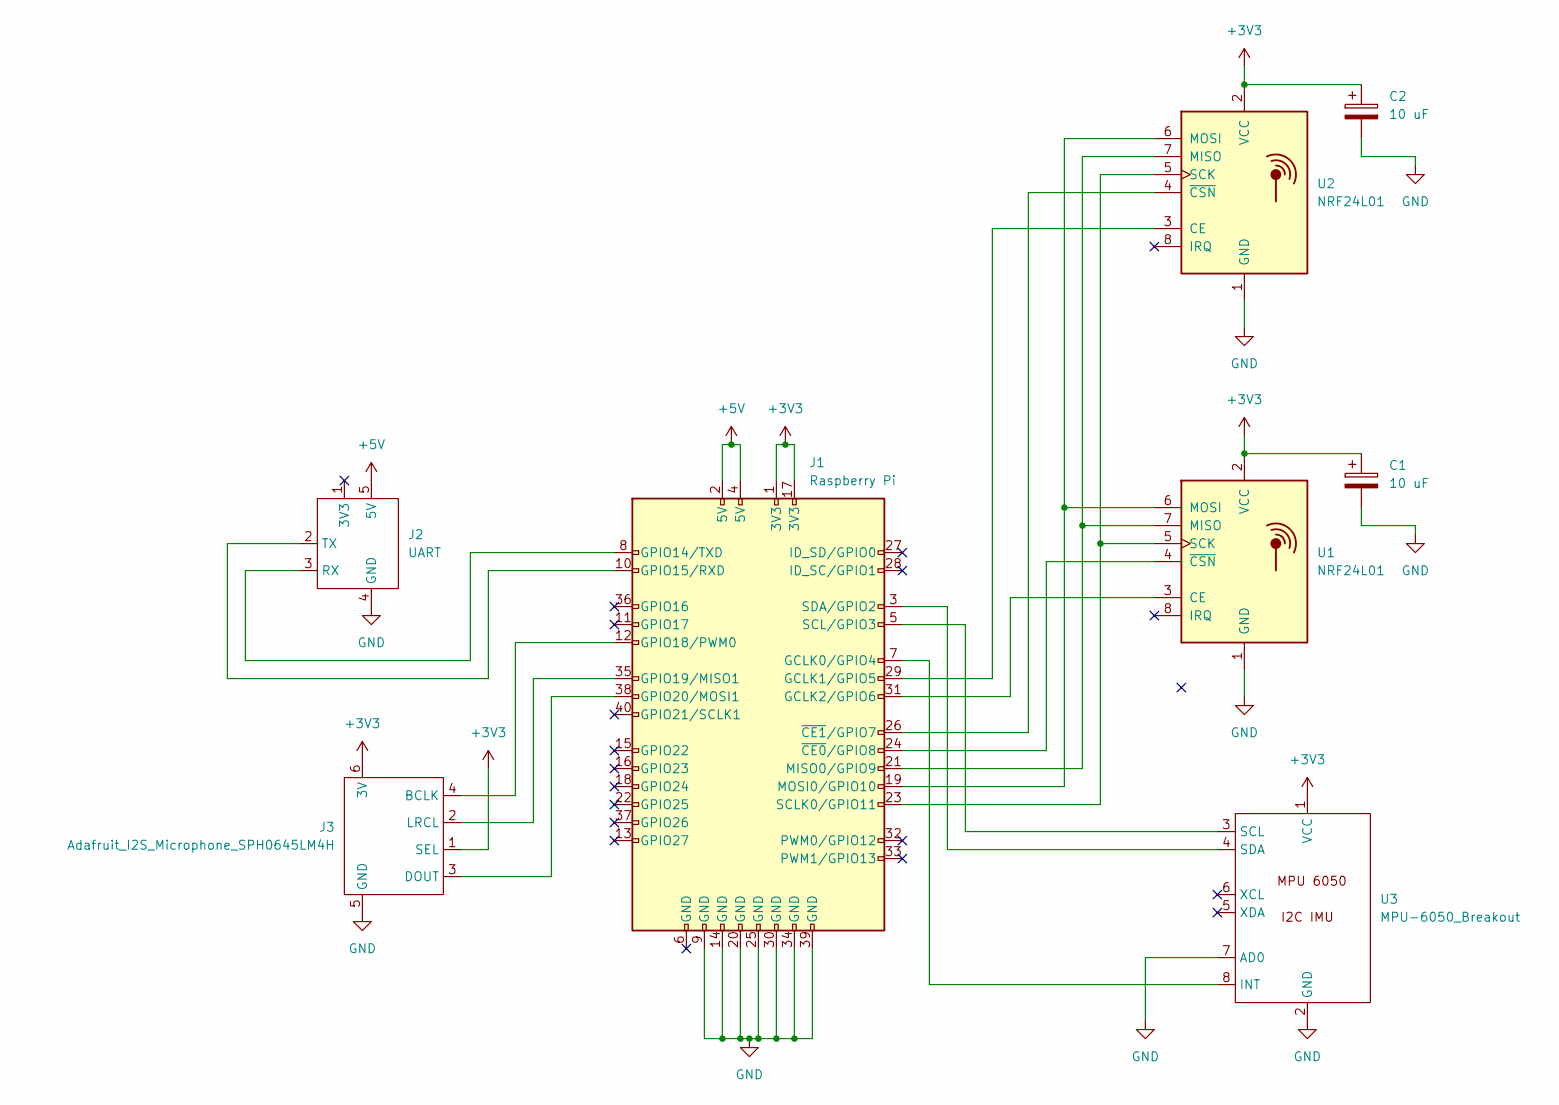
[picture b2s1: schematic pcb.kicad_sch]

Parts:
C1, C2: 10 uF; CP_Elec_4x5.4
J1: Raspberry Pi; PinSocket_2x20_P2.54mm_Vertical
J2: UART; PinSocket_1x05_P2.54mm_Horizontal
J3: Adafruit_I2S_Microphone_SPH0645LM4H; PinSocket_1x06_P2.54mm_Vertical
U1, U2: NRF24L01; nRF24L01_Breakout
U3: MPU-6050_Breakout; PinSocket_1x08_P2.54mm_Vertical

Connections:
+3V3: C1.1, C2.1, J1.1 (3V3), J1.17 (3V3), J3.1 (SEL), J3.6 (3V), U1.2 (VCC), U2.2 (VCC), U3.1 (VCC)
+5V: J1.2 (5V), J1.4 (5V), J2.5 (5V)
GND: C1.2, C2.2, J1.9 (GND), J1.14 (GND), J1.20 (GND), J1.25 (GND), J1.30 (GND), J1.34 (GND), J1.39 (GND), J2.4 (GND), J3.5 (GND), U1.1 (GND), U2.1 (GND), U3.2 (GND), U3.7 (AD0)
unnamed: J1.3 (SDA/GPIO2), U3.4 (SDA)
unnamed: J1.5 (SCL/GPIO3), U3.3 (SCL)
unnamed: J1.7 (GCLK0/GPIO4), U3.8 (INT)
unnamed: J1.8 (GPIO14/TXD), J2.3 (RX)
unnamed: J1.10 (GPIO15/RXD), J2.2 (TX)
unnamed: J1.12 (GPIO18/PWM0), J3.4 (BCLK)
unnamed: J1.19 (MOSI0/GPIO10), U1.6 (MOSI), U2.6 (MOSI)
unnamed: J1.21 (MISO0/GPIO9), U1.7 (MISO), U2.7 (MISO)
unnamed: J1.23 (SCLK0/GPIO11), U1.5 (SCK), U2.5 (SCK)
unnamed: J1.26 (~CE1/GPIO7), U2.4 (~CSN)
unnamed: J1.29 (GCLK1/GPIO5), U2.3 (CE)
unnamed: J1.35 (GPIO19/MISO1), J3.2 (LRCL)
unnamed: J1.38 (GPIO20/MOSI1), J3.3 (DOUT)
unnamed: J1.31 (GCLK2/GPIO6), U1.3 (CE)
unnamed: J1.24 (~CE0/GPIO8), U1.4 (~CSN)

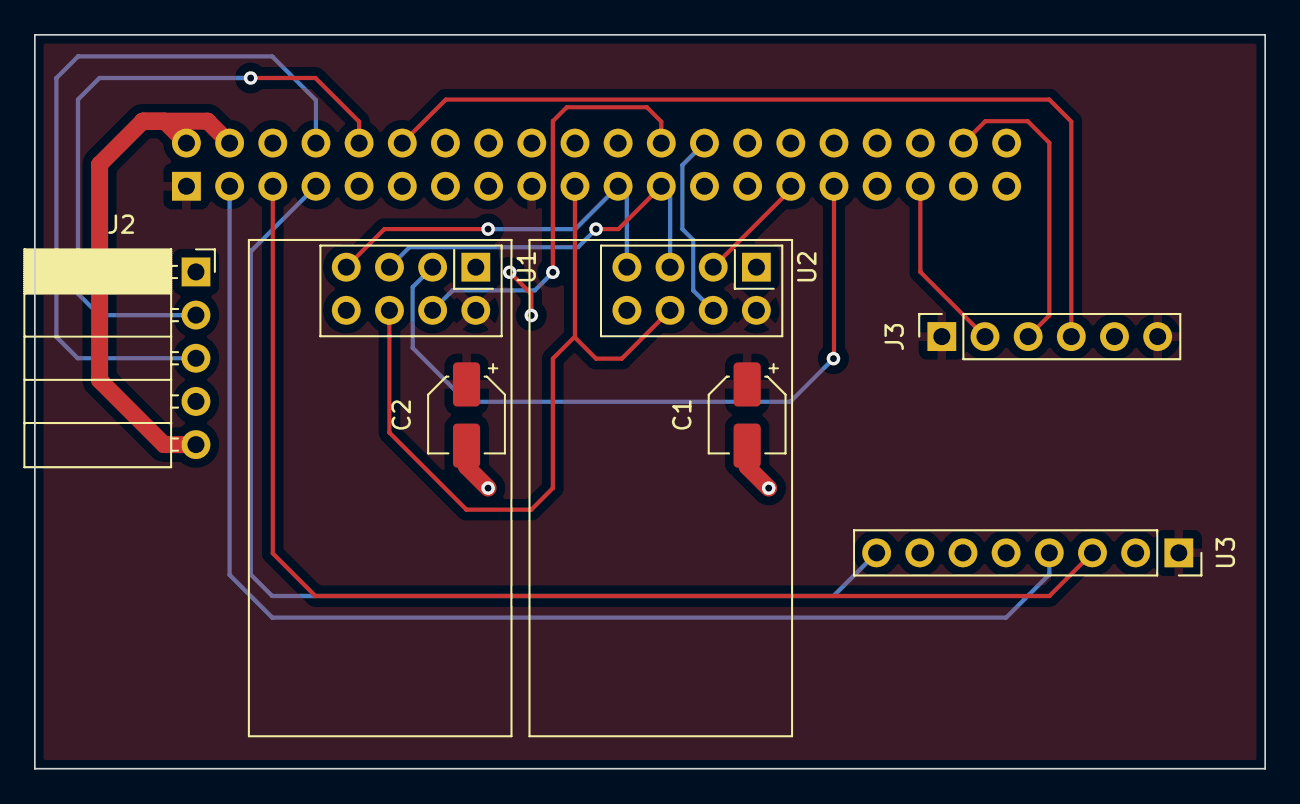
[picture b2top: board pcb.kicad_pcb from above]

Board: 2 copper layers, 72.4 x 43.2 mm, 8 parts (1 on the bottom side), 18 nets.

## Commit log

2022-03-28 minor
2022-03-30 done
2022-03-31 2020/2021 -> 2022
2022-04-13 done.
2022-04-13 stuff
2022-04-13 start of new lab
2022-04-19 readings
2022-04-21 start lab
2022-04-22 more tests
2022-04-23 next lab
2022-04-27 some code.
2022-04-27 new lab
2022-04-29 added libgcc
2022-05-05 new accel lab
2022-05-05 lab 5 partially done. On leak detector.
2022-05-05 gitignore
2022-05-15 Initial verilog installation instructions and prelab
2022-05-15 Add sv guide
2022-05-15 adding memcheck
2022-05-15 Update verilog prelab
2022-05-16 lab 5 mostly done. Slight bugs on tests 5 and 6
2022-05-17 add miscellaneous utilities to libpi
2022-05-17 Add verilog starter code
2022-05-17 Add hardware uart lab
2022-05-17 Add readme and adder
2022-05-17 Better readme
2022-05-17 Add extra info
2022-05-18 Update install instructions
2022-05-18 Add empty for checking installation
2022-05-18 Add adder synth target
2022-05-18 Wno-unoptflat
2022-05-18 Add uart simulator
2022-05-18 Lab 5 and 6 tests all pass.
2022-05-19 Add uart rx test
2022-05-19 Add uart tx test
2022-05-19 Update makefile
2022-05-24 Revert "Merge branch 'main' of https://github.com/dddrrreee/cs240lx-22spr into master"
    This reverts commit 856bccbb455c1ccd5d4efcc93f829d1ca4552234, reversing
    changes made to 3fb4cafad2cce314d76b718f5566a9827b7d2e31.
2022-05-25 lab7 done, no more staff-* calls
2022-05-25 lab8 done. Mic may be faulty? Implemented hardware i2c extension.
2022-05-26 lab9 interrupt checking working. Also cleanup build files from some folders and libpi
2022-10-03 added lab
2022-10-04 added dateasheet
2022-10-26 new lab unlocked.
2022-11-03 Add d prelab
2022-11-03 Simplify object.d
2022-11-03 Update links
2022-11-07 Add writeup
2022-11-07 starter code
2022-11-07 Instructions for building gdc from source
2022-11-07 Support older LDC inline asm syntax
2022-11-08 Remove rwx warning suppression
2022-11-08 draft readme for zig lab
2022-11-08 trivial
2022-11-10 major
2022-11-16 Adding prelab for lab 23.
2022-11-16 Add README for lab32-memcheck-llvm.
2022-11-16 Code for 23-memcheck-llvm
2022-11-17 Fix Makefile.
2022-11-17 Fix Typo in Makefile.
2022-11-28 upload the SAT lab
2022-11-28 Added SMT lab
2022-11-28 prelab
2022-11-28 A little bit less starter code
2022-11-28 add a gitignore
2022-11-29 xcheckp5
2022-11-30 micro
2022-11-30 minor test cases for smt solver
2022-12-01 parens
2022-12-01 make basic symex work without arrays
2022-12-05 RISC-V lab
2022-12-05 Add riscvtest to test suite
2023-01-14 fixed
